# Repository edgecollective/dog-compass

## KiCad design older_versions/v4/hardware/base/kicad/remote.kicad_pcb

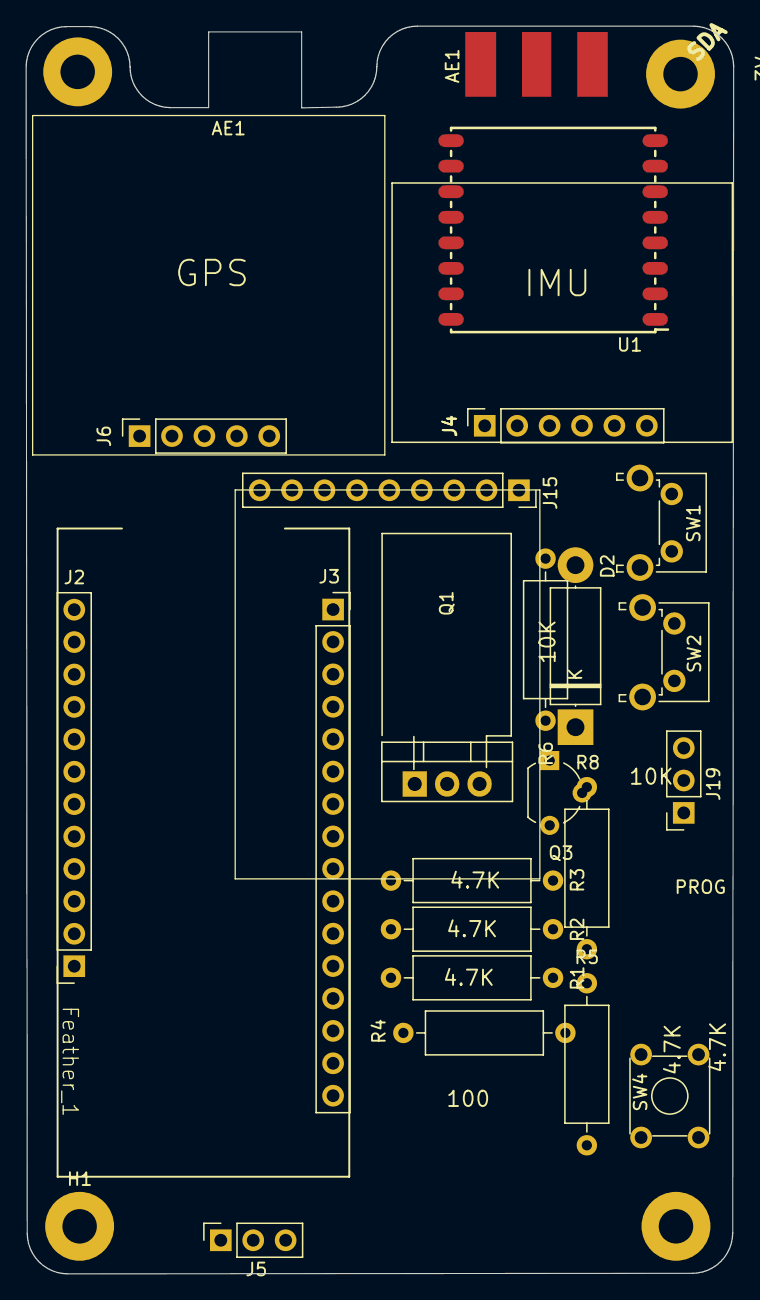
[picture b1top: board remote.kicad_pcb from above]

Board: 2 copper layers, 55.4 x 97.8 mm, 26 parts (0 on the bottom side), 20 nets, no tracks yet.

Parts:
AE1: Antenna_Shield; RF_SMA_BoardEdge_142-0701-801
D2: DIODE; D_5W_P12.70mm_Horizontal
H1, H2, H5, H6: MountingHole_Pad; MountingHole_2.7mm_M2.5_Pad
J2: Conn_01x12_Female; PinSocket_1x12_P2.54mm_Vertical
J3: Conn_01x16_Female; PinSocket_1x16_P2.54mm_Vertical
J4: Conn_01x06_Female; PinSocket_1x06_P2.54mm_Vertical
J5, J19: Conn_01x03_Female; PinSocket_1x03_P2.54mm_Vertical
J6: Conn_01x05_Female; PinSocket_1x05_P2.54mm_Vertical
J15: Conn_01x09_Female; PinSocket_1x09_P2.54mm_Vertical
Q1: Q_NMOS_GDS; TO-220-3_Vertical
Q3: Q_NPN_EBC; TO-92L_Wide
R1, R2, R3, R4: 4.7K; R_Axial_DIN0309_L9.0mm_D3.2mm_P12.70mm_Horizontal
R5, R8: R; R_Axial_DIN0309_L9.0mm_D3.2mm_P12.70mm_Horizontal
R6: 10K; R_Axial_DIN0309_L9.0mm_D3.2mm_P12.70mm_Horizontal
SW1, SW2: SW_Push; SW_Tactile_SPST_Angled_PTS645Vx58-2LFS
SW4: SW_Push_Dual; SW_TH_Tactile_Omron_B3F-10xx
U1: RFM95HW; RFM95

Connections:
+3V3: D2.1 (K), H2.1, J3.15, J4.1, J6.5, J15.1, R1.1, R2.1, R3.1, R4.1
A0: J3.12, R8.2
A3: J3.9, J19.3
A4: J3.8, R4.2, SW1.1
A5: J3.7, R3.2, SW2.1
D5: J2.10, J15.6
D9: J2.8, Q1.1 (G), R6.1
GND: J3.13, J4.3, J5.1, J15.3, Q1.3 (S), Q3.1 (E), R5.2, R6.2, SW1.2, SW2.2, SW4.3, SW4.4
MOSI: J3.5, J15.5
unnamed: D2.2 (A), Q3.3 (C)
unnamed: J19.2, R5.1
unnamed: Q3.2 (B), R8.1
POWER_1: J6.4, Q1.2 (D)
RX_D0: J3.3, J6.2
SCK: J3.6, J15.4
SCL: H6.1, J2.11, J4.4, R2.2
SDA: H5.1, J2.12, J4.5, R1.2
TX_D1: J3.2, J6.3
VBAT: J2.1, J5.2
~RESET: J3.16, SW4.1, SW4.2

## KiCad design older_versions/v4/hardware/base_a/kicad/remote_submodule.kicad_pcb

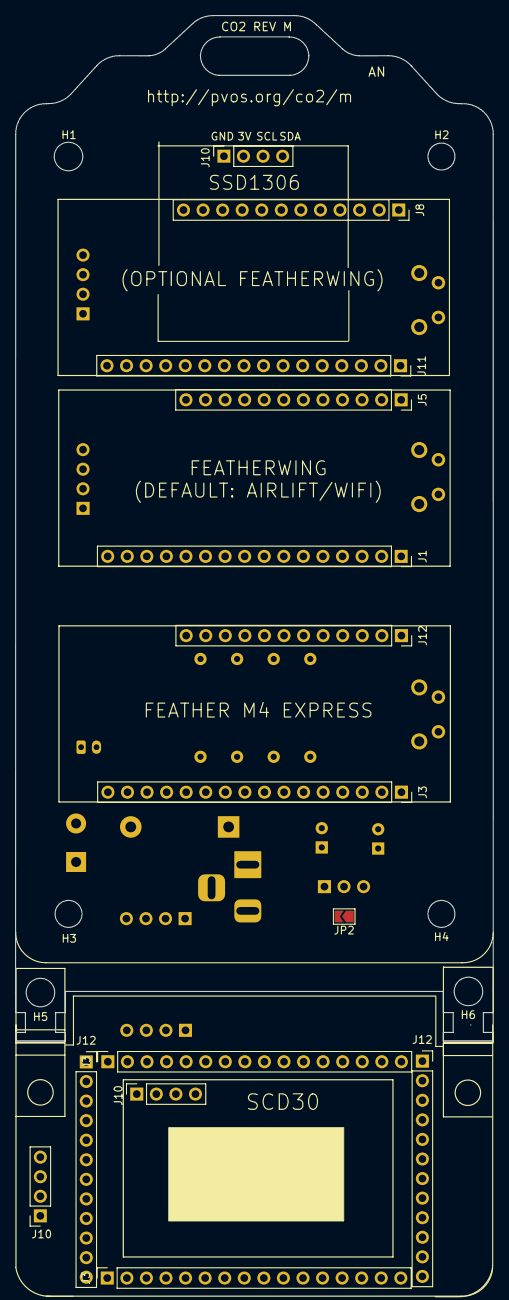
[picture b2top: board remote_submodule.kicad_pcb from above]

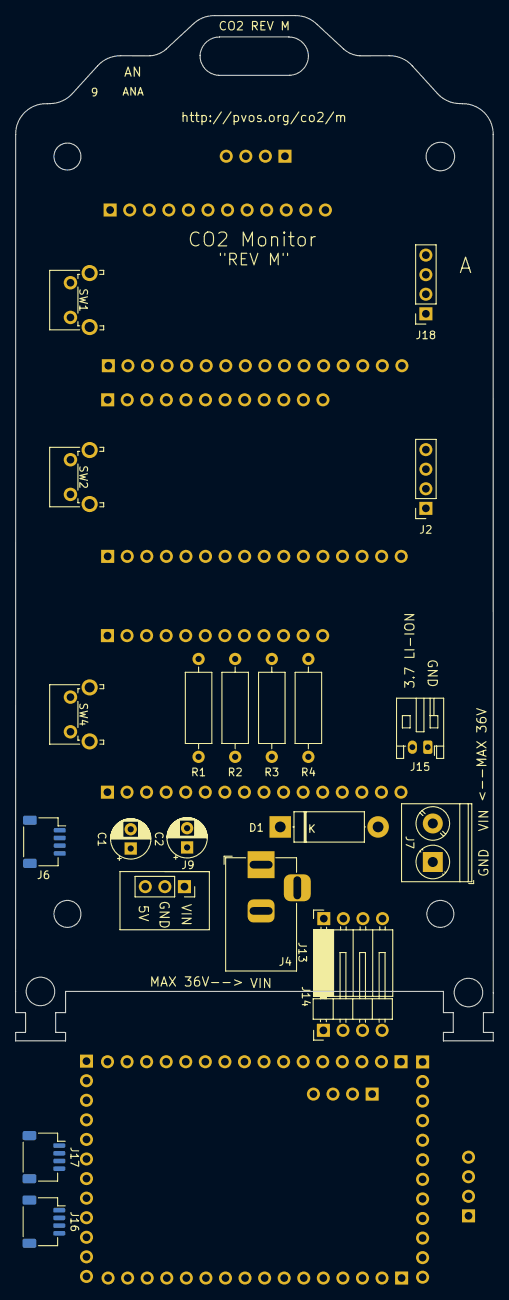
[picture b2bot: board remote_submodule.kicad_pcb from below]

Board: 2 copper layers, 62.0 x 133.1 mm, 41 parts (21 on the bottom side), 36 nets, no tracks yet.

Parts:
C1: 10uF; CP_Radial_D5.0mm_P2.50mm
C2: 22uF; CP_Radial_D5.0mm_P2.50mm
D1: D; D_5W_P12.70mm_Horizontal
H1, H5, H6: MountingHole; MountingHole_3.7mm
H2, H3, H4: MountingHole; MountingHole_3.5mm
J1, J3, J3#2, J3#3, J11: Conn_01x16_Female; PinSocket_1x16_P2.54mm_Vertical
J2, J10, J10#2, J10#3, J18: ssd1306; PinSocket_1x04_P2.54mm_Vertical
J4: Barrel_Jack_MountingPin; BarrelJack_Horizontal
J5, J8, J12, J12#2, J12#3: Conn_01x12_Female; PinSocket_1x12_P2.54mm_Vertical
J6, J16, J17: Conn_01x04_Female; JST_SH_SM04B-SRSS-TB_1x04-1MP_P1.00mm_Horizontal
J7: Screw_Terminal_01x02; TerminalBlock_Phoenix_PT-1,5-2-5.0-H_1x02_P5.00mm_Horizontal
J9: Conn_01x03_Female; PinSocket_1x03_P2.54mm_Vertical
J13: Conn_01x04_Female; PinSocket_1x04_P2.54mm_Horizontal
J14: Conn_01x04_Female; PinHeader_1x04_P2.54mm_Horizontal
J15: Conn_01x02_Female; JST_PH_S2B-PH-K_1x02_P2.00mm_Horizontal
JP2: Jumper_NO_Small; SolderJumper-2_P1.3mm_Open_TrianglePad1.0x1.5mm
R1, R2, R3, R4: 4.7K; R_Axial_DIN0309_L9.0mm_D3.2mm_P12.70mm_Horizontal
SW1, SW2, SW4: SW_Push; SW_Tactile_SPST_Angled_PTS645Vx58-2LFS

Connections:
3_BUTTON_B: R1.2, SW2.1
+3V3: J2.2, J6.2, J10.2, J10#2.2, J10#3.2, J16.2, J17.2, J18.2, R1.1, R2.1, R3.1, R4.1
A3_BUTTON_A: R2.2, SW1.1
GND: C1.1, C2.1, J2.1, J4.2, J6.1, J7.1, J9.2, J10.1, J10#2.1, J10#3.1, J16.1, J17.1, J18.1, SW1.2, SW2.2, SW4.2
unnamed: J3.1, J3#2.1, J3#3.1
unnamed: J3.2, J3#2.2, J3#3.2
unnamed: J3.3, J3#2.3, J3#3.3
unnamed: J3.4, J3#2.4, J3#3.4
unnamed: J3.5, J3#2.5, J3#3.5
unnamed: J3.6, J3#2.6, J3#3.6
unnamed: J3.7, J3#2.7, J3#3.7
unnamed: J3.8, J3#2.8, J3#3.8
unnamed: J3.9, J3#2.9, J3#3.9
unnamed: J3.10, J3#2.10, J3#3.10
unnamed: J3.11, J3#2.11, J3#3.11
unnamed: J3.12, J3#2.12, J3#3.12
unnamed: J3.13, J3#2.13, J3#3.13
unnamed: J3.14, J3#2.14, J3#3.14
unnamed: J3.15, J3#2.15, J3#3.15
unnamed: J3.16, J3#2.16, J3#3.16
unnamed: J12.1, J12#2.1, J12#3.1
unnamed: J12.2, J12#2.2, J12#3.2
unnamed: J12.3, J12#2.3, J12#3.3
unnamed: J12.4, J12#2.4, J12#3.4
unnamed: J12.5, J12#2.5, J12#3.5
unnamed: J12.6, J12#2.6, J12#3.6
unnamed: J12.7, J12#2.7, J12#3.7
unnamed: J12.8, J12#2.8, J12#3.8
unnamed: J12.9, J12#2.9, J12#3.9
unnamed: J12.10, J12#2.10, J12#3.10
unnamed: J12.11, J12#2.11, J12#3.11
unnamed: J12.12, J12#2.12, J12#3.12
SCL: J2.3, J6.4, J10.3, J10#2.3, J10#3.3, J16.4, J17.4, J18.3, R4.2
SDA: J2.4, J6.3, J10.4, J10#2.4, J10#3.4, J16.3, J17.3, J18.4, R3.2
VIN_DCDC: C1.2, J4.1, J9.1, JP2.2
VOUT_DCDC: C2.2, D1.2, J9.3, JP2.1

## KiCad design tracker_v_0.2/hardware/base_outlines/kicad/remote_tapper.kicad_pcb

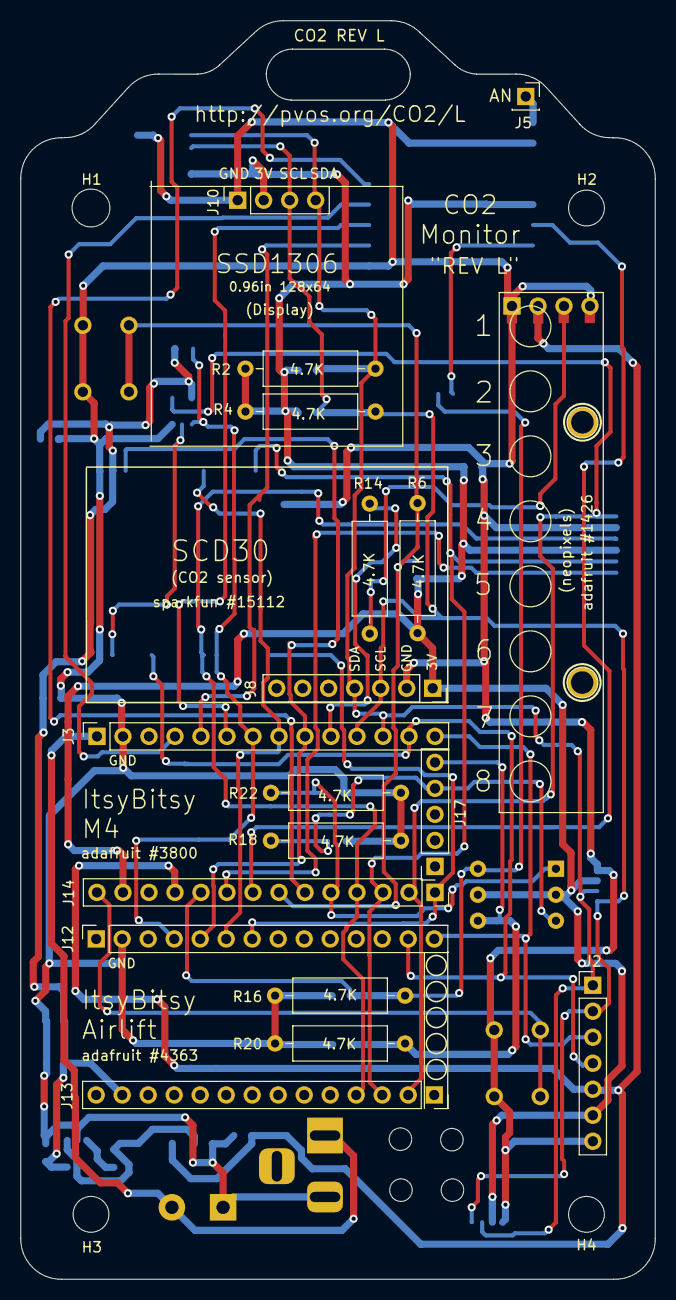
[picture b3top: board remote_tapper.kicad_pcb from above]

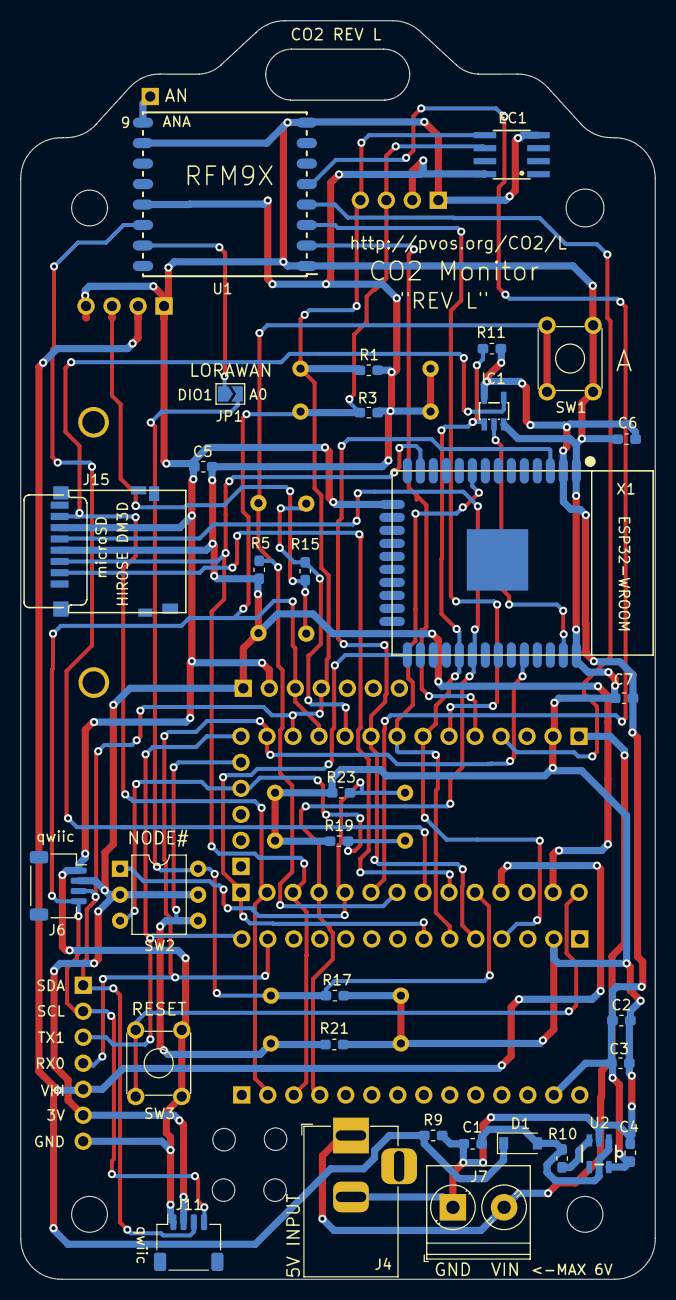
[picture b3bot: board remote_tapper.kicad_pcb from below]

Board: 2 copper layers, 62.0 x 122.9 mm, 65 parts (33 on the bottom side), 35 nets.

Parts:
C1, C3, C4, C7: 10u; C_0603_1608Metric_Pad1.05x0.95mm_HandSolder
C2, C6: 0.1u; C_0603_1608Metric_Pad1.05x0.95mm_HandSolder
C5: 1u; C_0603_1608Metric_Pad1.05x0.95mm_HandSolder
D1: DIODE; D_SOD-123
EC1: ATECC108; SOIC8
H1: MountingHole; MountingHole_3.7mm
H2, H3, H4: MountingHole; MountingHole_3.5mm
H5, H6: MountingHole; MOUNTINGHOLE_2.0_PLATED
H7, H8, H9, H10: MountingHole; MountingHole_2.2mm_M2
IC1: 74AHC1G125; SOT23-5L
J1: Conn_01x04_Female; PinSocket_1x04_P2.54mm_Vertical_no_silk
J2: Conn_01x07_Female; PinHeader_1x07_P2.54mm_Vertical
J3, J12, J13, J14: Conn_01x14_Female; PinSocket_1x14_P2.54mm_Vertical
J4: Barrel_Jack_MountingPin; BarrelJack_Horizontal
J5: Conn_01x01_Female; PinSocket_1x01_P2.54mm_Vertical
J6, J11: Conn_01x04_Female; JST_SH_SM04B-SRSS-TB_1x04-1MP_P1.00mm_Horizontal
J7: Screw_Terminal_01x02; TerminalBlock_Phoenix_PT-1,5-2-5.0-H_1x02_P5.00mm_Horizontal
J8: SCD30; PinSocket_1x07_P2.54mm_Vertical
J10: ssd1306; PinSocket_1x04_P2.54mm_Vertical
J15: Micro_SD_Card; DM3D-SF_outline
J17: Conn_01x05_Female; PinSocket_1x05_P2.54mm_Vertical
JP1: Jumper_NO_Small; SolderJumper-2_P1.3mm_Open_TrianglePad1.0x1.5mm
R1, R3: R; R_0603_1608Metric_Pad1.05x0.95mm_HandSolder
R2, R4: R; R_Axial_DIN0309_L9.0mm_D3.2mm_P12.70mm_Horizontal
R5, R17, R19, R21, R23: 4.7K; R_0603_1608Metric_Pad1.05x0.95mm_HandSolder
R6, R16, R18, R20, R22: 4.7K; R_Axial_DIN0309_L9.0mm_D3.2mm_P12.70mm_Horizontal
R9, R10: 100k; R_0603_1608Metric_Pad1.05x0.95mm_HandSolder
R11: 10K; R_0603_1608Metric_Pad1.05x0.95mm_HandSolder
R14: 500; R_Axial_DIN0309_L9.0mm_D3.2mm_P12.70mm_Horizontal
R15: 500; R_0603_1608Metric_Pad1.05x0.95mm_HandSolder
SW1, SW3: SW_Push_Dual; SW_TH_Tactile_Omron_B3F-10xx
SW2: SW_Coded_SH-7010; sd2010_dip
TP1, TP2, TP3, TP4: TestPoint; TestPoint_Pad_1.0x1.0mm_no_silk
U1: RFM95HW; RFM95
U2: VREG_SOT23-5; SOT23-5
X1: ESP32_WROOM32; ESP32-WROOM

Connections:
2_ESP_GPIO0: J12.7, J14.1, X1.25
3VESP: C2.1, C3.1, C4.1, C6.1, C7.1, IC1.5, J13.13, R11.1, U2.5, X1.2
3_LDO_ENABLE: J17.4, R18.1, R19.1, SW2.4
4_SERDAT: J17.5, R20.1, R21.1, SW2.2
5_NEOPIXEL: J3.10, R14.2, R15.2
7_ESP_RESET: J3.9, J12.5, X1.3
9_ESP_BUSY: J3.8, J12.6, X1.9
10_ESP_CS: IC1.1, J3.7, J12.4, R11.2, X1.29
11_LORA_MOSI: J3.6, U1.3
12_LORA_MISO: J3.5, U1.2
13_LORA_SCK: J3.4, U1.4
+3V3: C5.1, EC1.8, J2.6, J6.2, J8.1, J10.2, J11.2, J14.13, J15.4, R1.1, R2.1, R3.1, R4.1, R5.1, R6.1, SW2.C, U1.13
A0_LORAWAN: J14.10, JP1.2, R16.1, R17.1, SW2.8
A1_SD_CS: J14.9, J15.2
A2_LORA_IRQ: J14.8, U1.14
A3_BUTTON_A: J14.7, R5.2, R6.2, SW1.1, SW1.2
A4_LORA_CS: J14.6, U1.5
A5_BUTTON_B: J14.5, R22.1, R23.1, SW2.1
ESP_MISO: IC1.2, X1.37
ESP_RX: J2.4, J3.13, J12.13, X1.34
EXP_TX: J2.3, J3.14, J12.14
GND: C1.2, C2.2, C3.2, C4.2, C5.2, C6.2, C7.2, EC1.4, IC1.3, J1.1, J1.4, J2.7, J3.2, J4.2, J6.1, J7.1, J8.2, J10.1, J11.1, J12.2, J15.6, R9.2, R16.2, R17.2, R18.2, R19.2, R20.2, R21.2, R22.2, R23.2, SW1.3, SW1.4, SW3.3, SW3.4, TP1.1, TP4.1, U1.1, U1.8, U1.10, U2.2, X1.1, X1.15, X1.38
LORA_DIO1: JP1.1, U1.15
MISO: IC1.4, J13.2, J14.2, J15.7
MOSI: J13.3, J14.3, J15.3, X1.13
unnamed: C1.1, D1.2, R10.1, U2.1
unnamed: J1.3, R14.1, R15.1, TP3.1
unnamed: J5.1, U1.9
unnamed: R10.2, U2.3
SCK: J13.4, J14.4, J15.5, X1.30
SCL: EC1.6, J2.2, J3.11, J6.4, J8.3, J10.3, J11.4, R3.2, R4.2
SDA: EC1.5, J2.1, J3.12, J6.3, J8.4, J10.4, J11.3, R1.2, R2.2
VBAT: J3.1, J4.1, J7.2
VHI: D1.1, J1.2, J2.5, J14.11, R9.1, TP2.1
~RESET: J14.14, SW3.1, SW3.2

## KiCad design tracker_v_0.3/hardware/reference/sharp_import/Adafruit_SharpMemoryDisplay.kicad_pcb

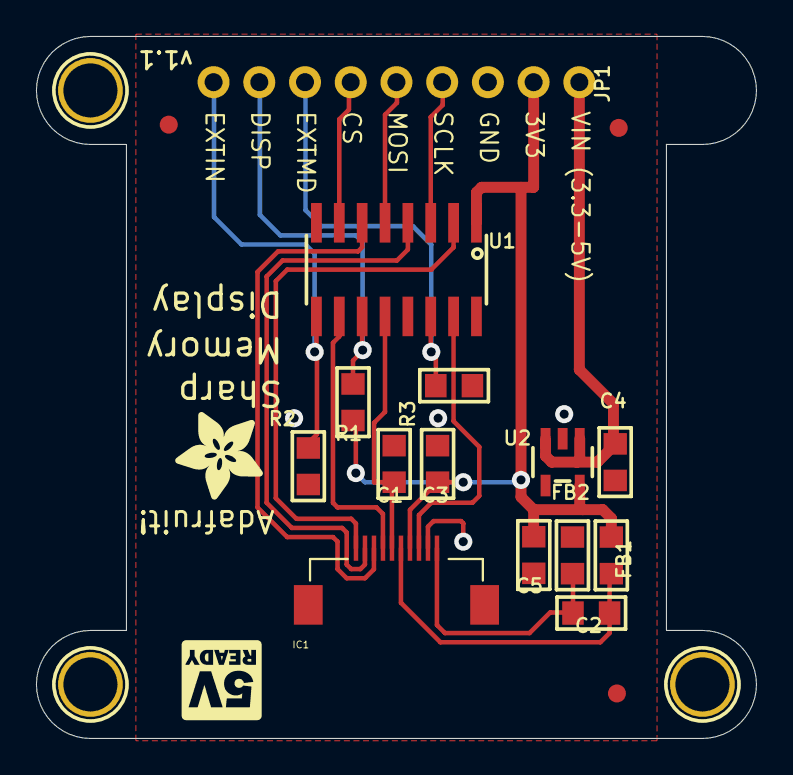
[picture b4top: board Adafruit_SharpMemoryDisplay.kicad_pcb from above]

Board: 16 copper layers, 40.0 x 39.0 mm, 22 parts (0 on the bottom side), 17 nets.

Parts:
C1: 0.1µF; _0805
C2, C3: 1µF; _0805
C4, C5: 10µF; _0805
FB1, FB2: FERRITE_0805; _0805
FID1, FID2, FID3: FIDUCIAL; FIDUCIAL_1MM
IC1: LS013B4DN04; FPC_10PIN_52892-1095
JP1: HEADER-1X970MIL; 1X09_ROUND_70
R1, R2, R3: 10K; _0805
U1: 74HC4050D; SOIC16
U2: MCP1824T-3302E/OT; SOT23-5
U$19: LOGIC_5VREADY_5MM
U$21, U$22, U$28: MOUNTINGHOLE3.0THIN; MOUNTINGHOLE_3.0_PLATEDTHIN
U$29: ADAFRUIT_5MM

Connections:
3.3V: C3.1, C5.1, FB1.1, IC1.P$7, JP1.2, R1.1, U1.1, U2.5
/DISP: C1.1, IC1.P$5, U1.12
/DISP_5V: JP1.8, R1.2, U1.11
/EXTCOMIN: IC1.P$4, U1.10
/EXTCOMIN_5V: JP1.9, R2.1, U1.9
/EXTMODE: IC1.P$8, U1.15
/EXTMODE_5V: JP1.7, R3.2, U1.14
/SCLK: IC1.P$1, U1.2
/SCLK_5V: JP1.4, U1.3
/SCS: IC1.P$3, U1.6
/SCS_5V: JP1.6, U1.7
/SI: IC1.P$2, U1.4
/SI_5V: JP1.5, U1.5
AGND: C2.2, FB2.2, IC1.P$10
AVDD: C2.1, FB1.2, IC1.P$6
GND: C1.2, C3.2, C4.2, C5.2, FB2.1, IC1.P$9, JP1.3, R2.2, R3.1, U1.8, U2.2
VIN: C4.1, JP1.1, U2.1, U2.3
